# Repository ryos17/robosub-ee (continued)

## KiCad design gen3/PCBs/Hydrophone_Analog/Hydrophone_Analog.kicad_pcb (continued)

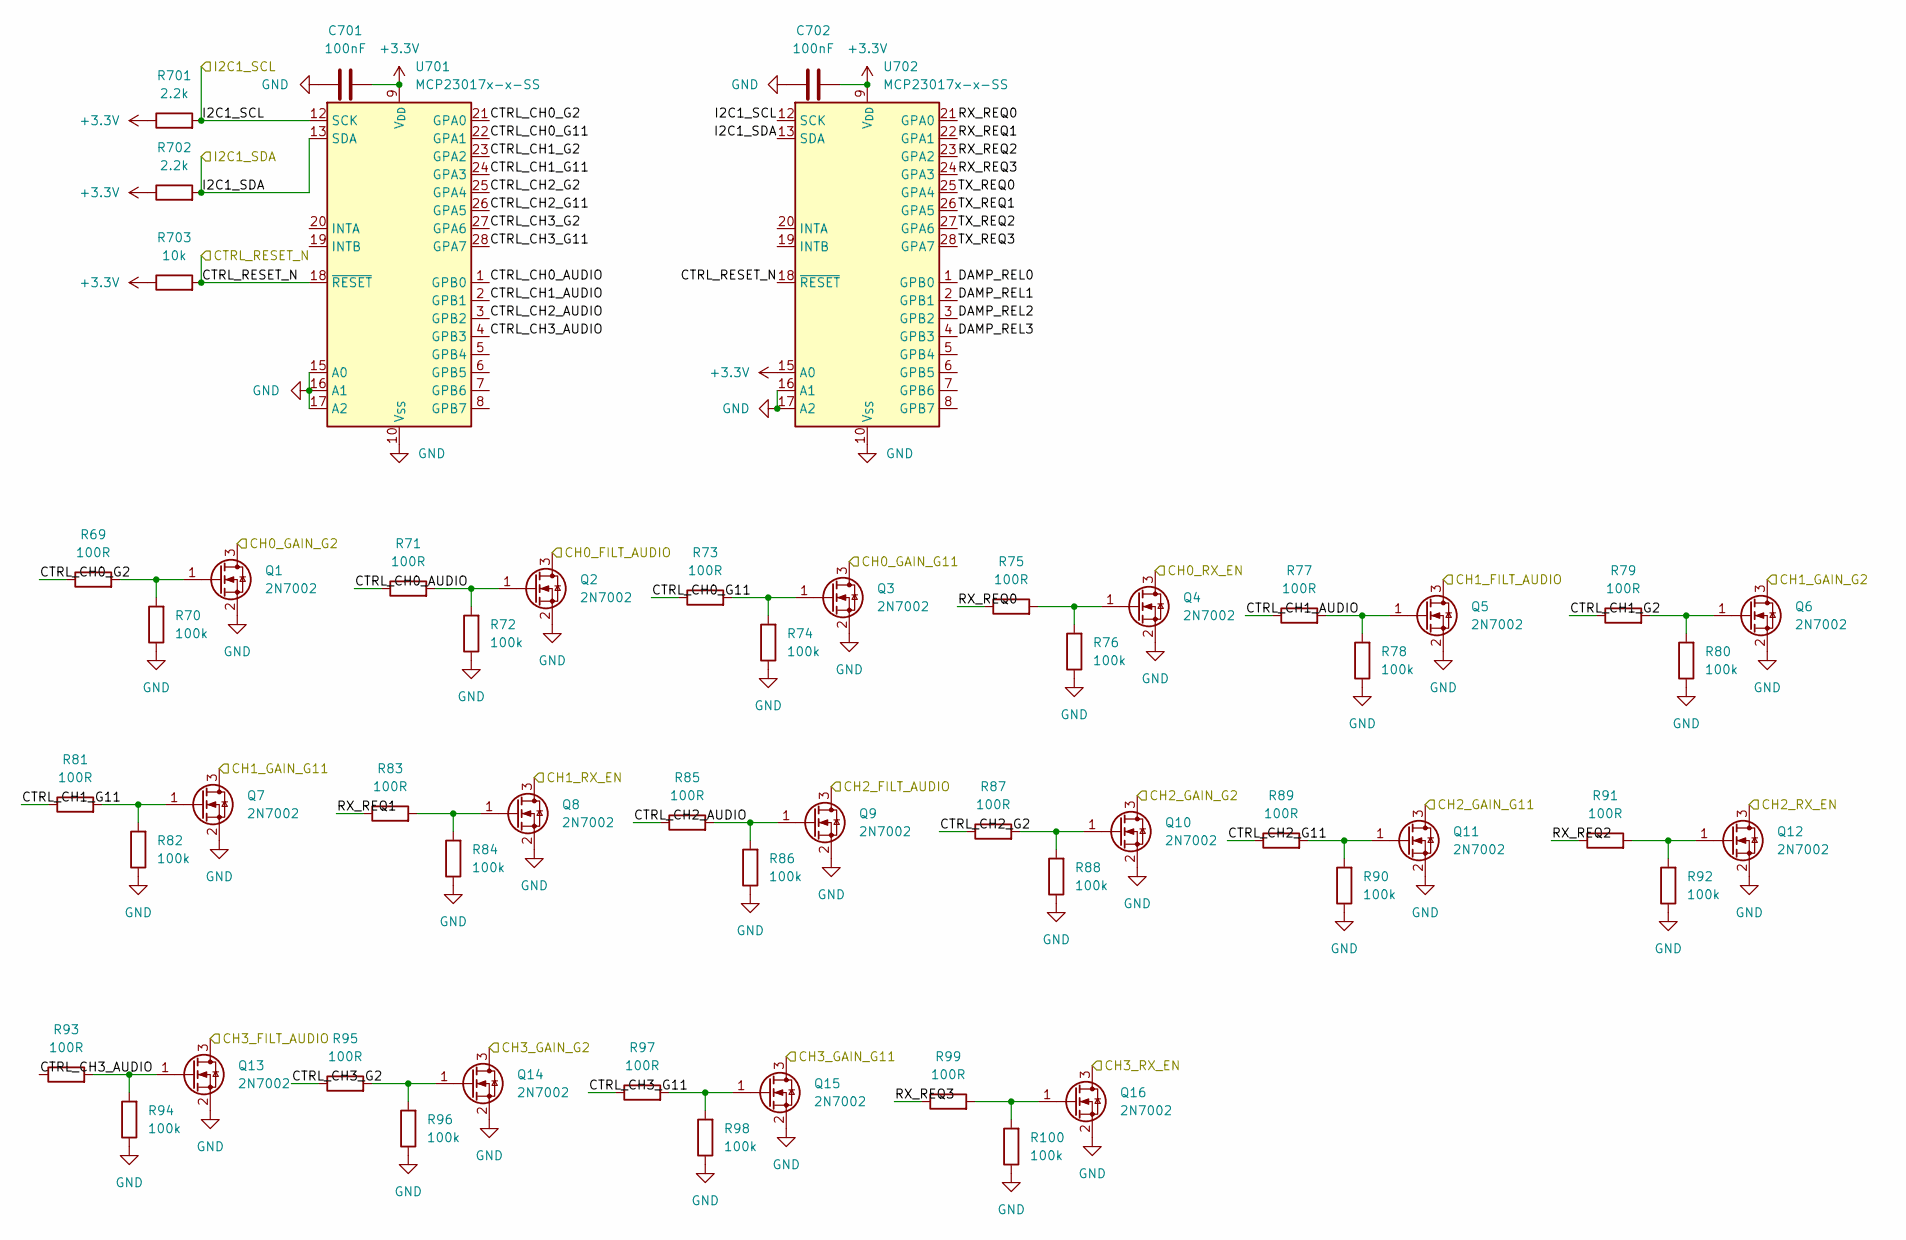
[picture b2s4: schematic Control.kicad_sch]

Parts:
C701, C702: 100nF; C_0805_2012Metric
Q1, Q2, Q3, Q4, Q5, Q6, Q7, Q8, Q9, Q10, Q11, Q12, Q13, Q14, Q15, Q16: 2N7002; SOT-23
R69, R71, R73, R75, R77, R79, R81, R83, R85, R87, R89, R91, R93, R95, R97, R99: 100R; R_0805_2012Metric
R70, R72, R74, R76, R78, R80, R82, R84, R86, R88, R90, R92, R94, R96, R98, R100: 100k; R_0805_2012Metric
R701, R702: 2.2k; R_0805_2012Metric
R703: 10k; R_0805_2012Metric
U701, U702: MCP23017x-x-SS; SSOP-28_5.3x10.2mm_P0.65mm

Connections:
+3.3V: C701.2, C702.2, R701.1, R702.1, R703.1, U701.9 (V_{DD}), U702.9 (V_{DD}), U702.15 (A0); also elsewhere on the board
/CH0_FILT_AUDIO: Q2.3 (D); also elsewhere on the board
/CH0_GAIN_G2: Q1.3 (D); also elsewhere on the board
/CH0_GAIN_G11: Q3.3 (D); also elsewhere on the board
/CH0_RX_EN: Q4.3 (D); also elsewhere on the board
/CH1_FILT_AUDIO: Q5.3 (D); also elsewhere on the board
/CH1_GAIN_G2: Q6.3 (D); also elsewhere on the board
/CH1_GAIN_G11: Q7.3 (D); also elsewhere on the board
/CH1_RX_EN: Q8.3 (D); also elsewhere on the board
/CH2_FILT_AUDIO: Q9.3 (D); also elsewhere on the board
/CH2_GAIN_G2: Q10.3 (D); also elsewhere on the board
/CH2_GAIN_G11: Q11.3 (D); also elsewhere on the board
/CH2_RX_EN: Q12.3 (D); also elsewhere on the board
/CH3_FILT_AUDIO: Q13.3 (D); also elsewhere on the board
/CH3_GAIN_G2: Q14.3 (D); also elsewhere on the board
/CH3_GAIN_G11: Q15.3 (D); also elsewhere on the board
/CH3_RX_EN: Q16.3 (D); also elsewhere on the board
/CTRL_RESET_N: R703.2, U701.18 (~RESET), U702.18 (~RESET); also elsewhere on the board
/Control/CTRL_CH0_AUDIO: R71.1, U701.1 (GPB0)
/Control/CTRL_CH0_G2: R69.1, U701.21 (GPA0)
/Control/CTRL_CH0_G11: R73.1, U701.22 (GPA1)
/Control/CTRL_CH1_AUDIO: R77.1, U701.2 (GPB1)
/Control/CTRL_CH1_G2: R79.1, U701.23 (GPA2)
/Control/CTRL_CH1_G11: R81.1, U701.24 (GPA3)
/Control/CTRL_CH2_AUDIO: R85.1, U701.3 (GPB2)
/Control/CTRL_CH2_G2: R87.1, U701.25 (GPA4)
/Control/CTRL_CH2_G11: R89.1, U701.26 (GPA5)
/Control/CTRL_CH3_AUDIO: R93.1, U701.4 (GPB3)
/Control/CTRL_CH3_G2: R95.1, U701.27 (GPA6)
/Control/CTRL_CH3_G11: R97.1, U701.28 (GPA7)
/Control/DAMP_REL0: U702.1 (GPB0)
/Control/DAMP_REL1: U702.2 (GPB1)
/Control/DAMP_REL2: U702.3 (GPB2)
/Control/DAMP_REL3: U702.4 (GPB3)
/Control/RX_REQ0: R75.1, U702.21 (GPA0)
/Control/RX_REQ1: R83.1, U702.22 (GPA1)
/Control/RX_REQ2: R91.1, U702.23 (GPA2)
/Control/RX_REQ3: R99.1, U702.24 (GPA3)
/Control/TX_REQ0: U702.25 (GPA4)
/Control/TX_REQ1: U702.26 (GPA5)
/Control/TX_REQ2: U702.27 (GPA6)
/Control/TX_REQ3: U702.28 (GPA7)
/I2C1_SCL: R701.2, U701.12 (SCK), U702.12 (SCK); also elsewhere on the board
/I2C1_SDA: R702.2, U701.13 (SDA), U702.13 (SDA); also elsewhere on the board
GND: C701.1, C702.1, Q1.2 (S), Q2.2 (S), Q3.2 (S), Q4.2 (S), Q5.2 (S), Q6.2 (S), Q7.2 (S), Q8.2 (S), Q9.2 (S), Q10.2 (S), Q11.2 (S), Q12.2 (S), Q13.2 (S), Q14.2 (S), Q15.2 (S), Q16.2 (S), R70.1, R72.1, R74.1, R76.1, R78.1, R80.1, R82.1, R84.1, R86.1, R88.1, R90.1, R92.1, R94.1, R96.1, R98.1, R100.1, U701.10 (V_{SS}), U701.15 (A0), U701.16 (A1), U701.17 (A2), U702.10 (V_{SS}), U702.16 (A1), U702.17 (A2); also elsewhere on the board
unnamed: Q1.1 (G), R69.2, R70.2
unnamed: Q2.1 (G), R71.2, R72.2
unnamed: Q3.1 (G), R73.2, R74.2
unnamed: Q4.1 (G), R75.2, R76.2
unnamed: Q5.1 (G), R77.2, R78.2
unnamed: Q6.1 (G), R79.2, R80.2
unnamed: Q7.1 (G), R81.2, R82.2
unnamed: Q8.1 (G), R83.2, R84.2
unnamed: Q9.1 (G), R85.2, R86.2
unnamed: Q10.1 (G), R87.2, R88.2
unnamed: Q11.1 (G), R89.2, R90.2
unnamed: Q12.1 (G), R91.2, R92.2
unnamed: Q13.1 (G), R93.2, R94.2
unnamed: Q14.1 (G), R95.2, R96.2
unnamed: Q15.1 (G), R97.2, R98.2
unnamed: Q16.1 (G), R99.2, R100.2

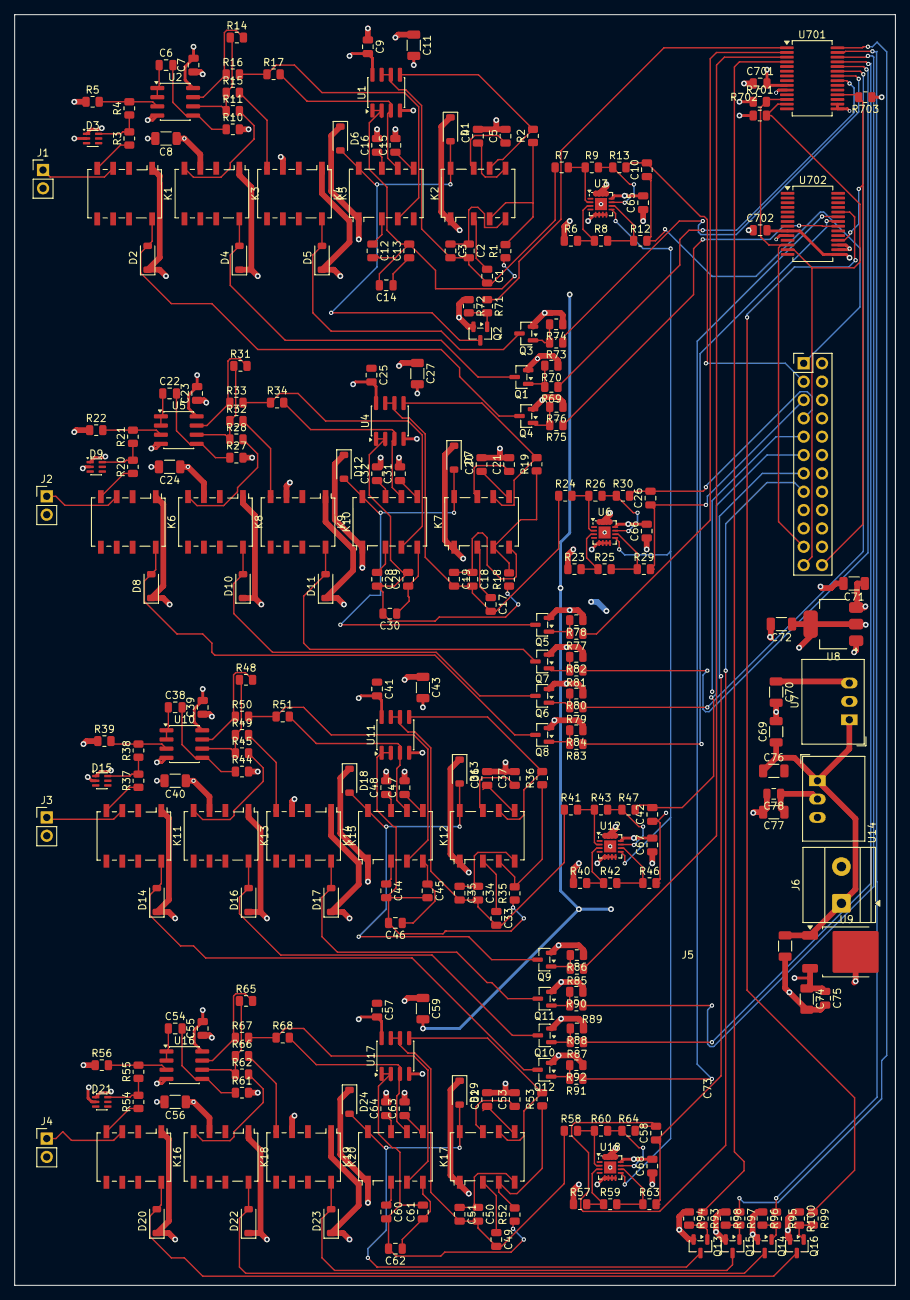
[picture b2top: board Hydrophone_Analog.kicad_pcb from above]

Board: 4 copper layers, 121.9 x 175.9 mm, 267 parts (0 on the bottom side), 178 nets.

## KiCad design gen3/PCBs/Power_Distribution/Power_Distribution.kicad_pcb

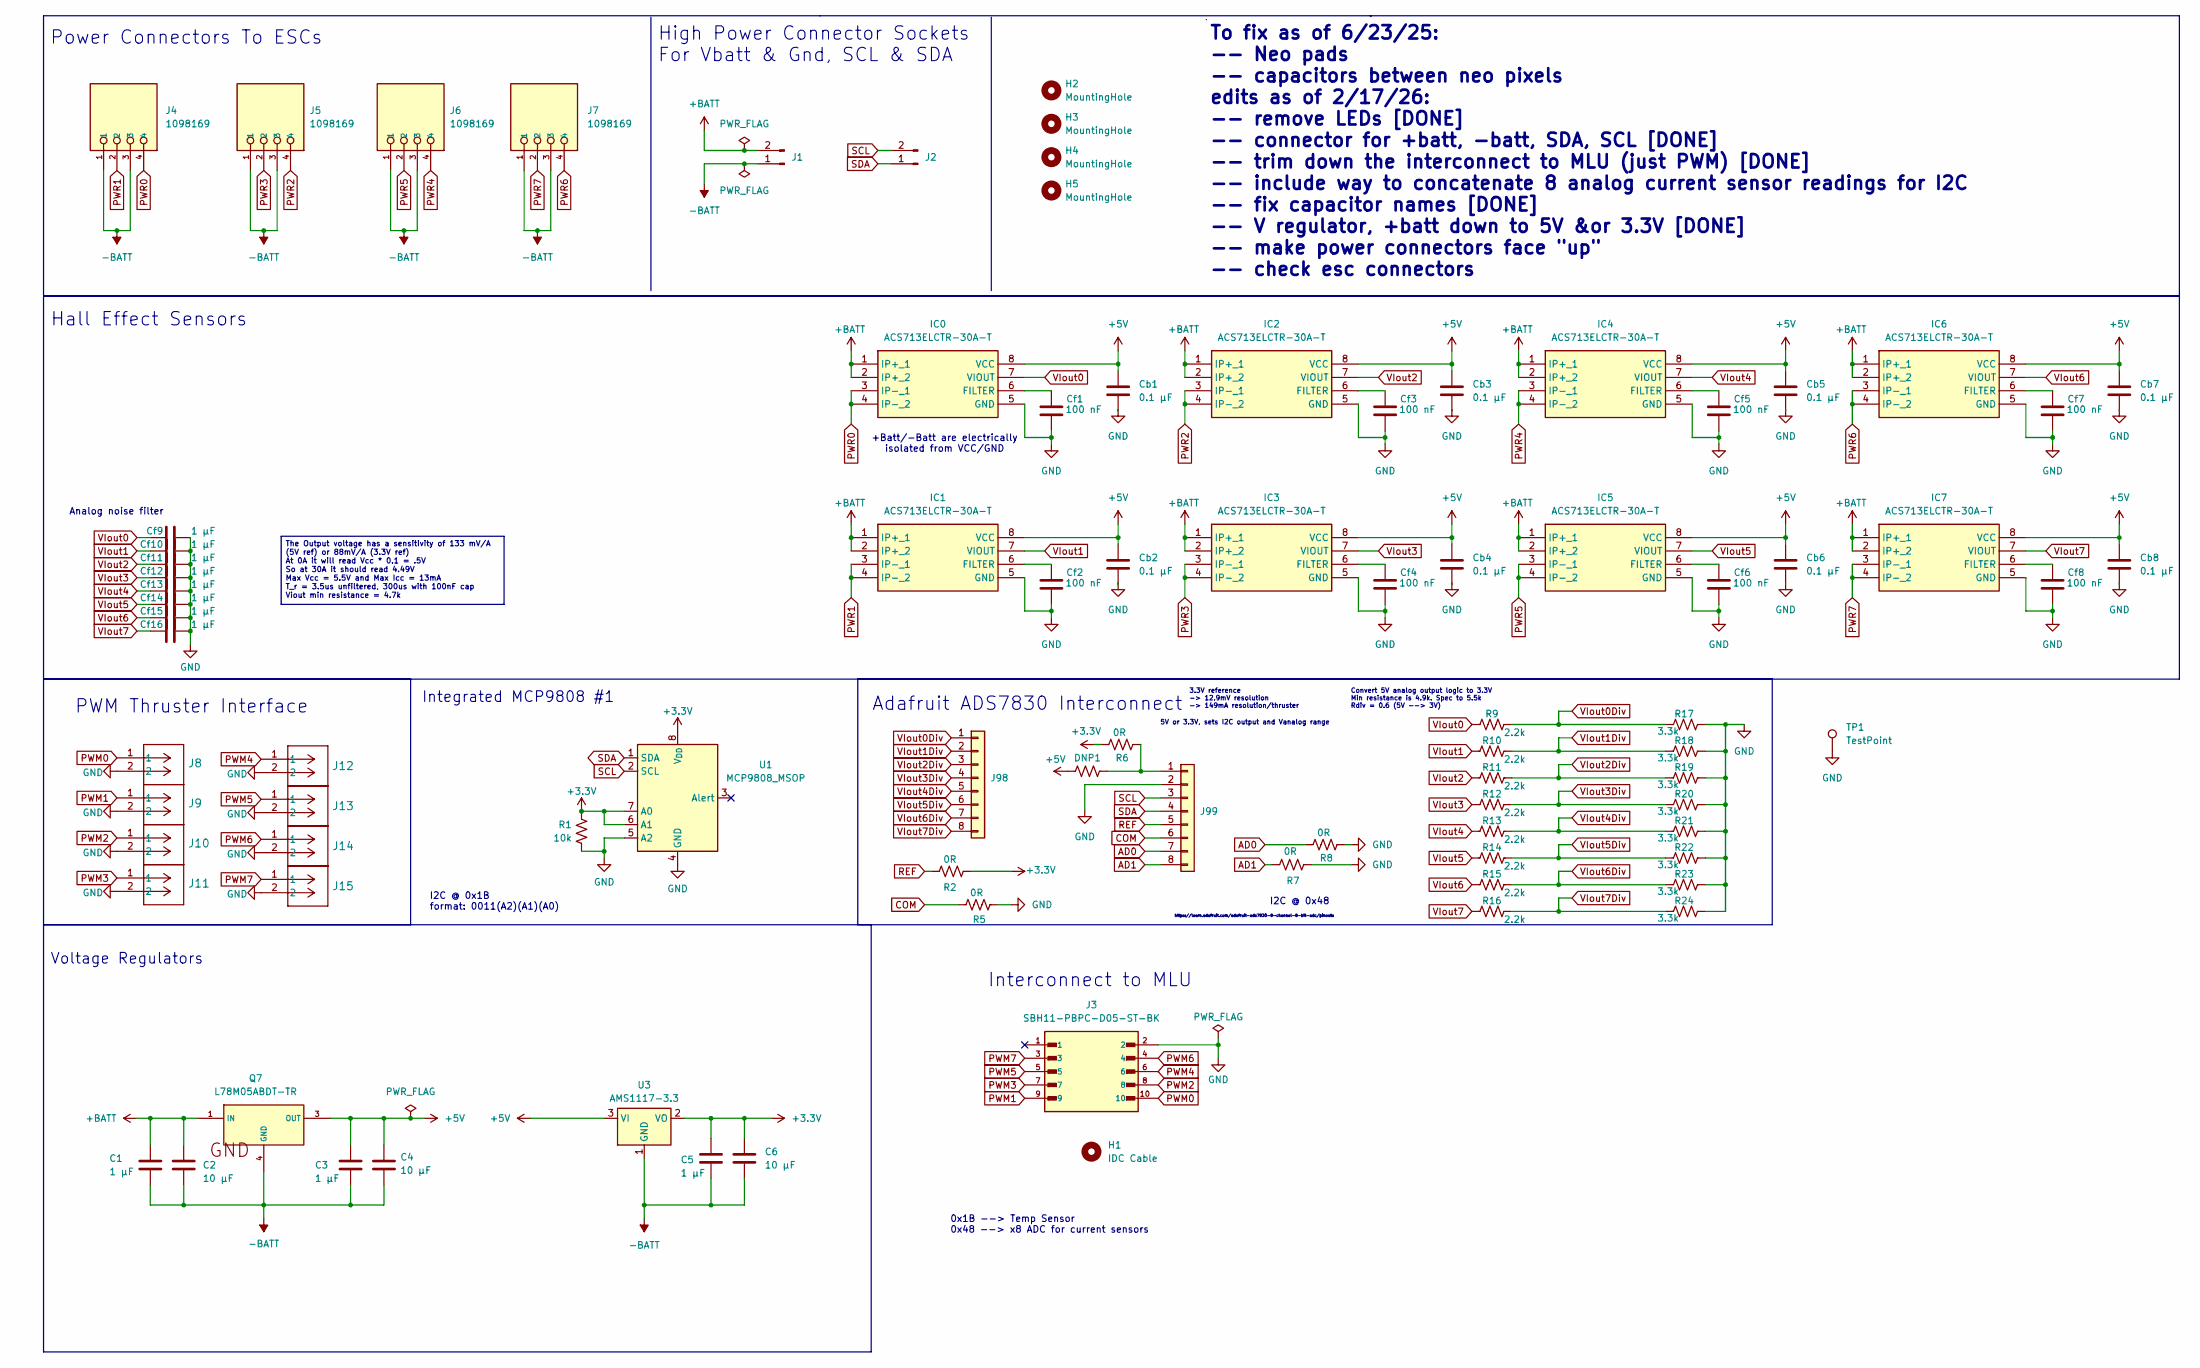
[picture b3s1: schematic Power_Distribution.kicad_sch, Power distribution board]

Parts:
C1, C3, C5: 1 µF; C_0805_2012Metric
C2, C4, C6: 10 µF; C_0805_2012Metric
Cb1, Cb2, Cb3, Cb4, Cb5, Cb6, Cb7, Cb8: 0.1 µF; C_0805_2012Metric_Pad1.18x1.45mm_HandSolder
Cf1, Cf2, Cf3, Cf4, Cf5, Cf6, Cf7, Cf8: 100 nF; C_0805_2012Metric_Pad1.18x1.45mm_HandSolder
Cf9, Cf10, Cf11, Cf12, Cf13, Cf14, Cf15, Cf16: 1 µF; C_0805_2012Metric_Pad1.18x1.45mm_HandSolder
DNP1: 0; R_0805_2012Metric
H1: IDC Cable
H2, H3, H4, H5: MountingHole; MountingHole_4.3mm_M4
IC0, IC1, IC2, IC3, IC4, IC5, IC6, IC7: ACS713ELCTR-30A-T; ACS711ELCTR25ABT; Manufacturer_Part_Number ACS713ELCTR-30A-T
J1: Conn_01x02_Pin; AMASS_XT60IPW-M_1x03_P7.20mm_Horizontal
J2: Conn_01x02_Pin; AMASS_XT30PW-F_1x02_P2.50mm_Horizontal
J3: SBH11-PBPC-D05-ST-BK; SULLINS_SBH11-PBPC-D05-ST-BK; PARTREV J
J4, J5, J6, J7: 1098169; PHOENIX_1098169
J8, J9, J10, J11, J12, J13, J14, J15: 430450212; Molex_Micro-Fit_3.0_43045-0212_2x01_P3.00mm_Vertical
J98, J99: Conn_01x08; PinHeader_1x08_P2.54mm_Vertical
Q7: L78M05ABDT-TR; TO-252-2_L6.5-W6.1-P4.58-LS10.0-TL; LCSC C58069
R1: 10k; R_0805_2012Metric_Pad1.20x1.40mm_HandSolder
R2, R5, R6, R7, R8: 0R; R_0805_2012Metric_Pad1.20x1.40mm_HandSolder
R9, R10, R11, R12, R13, R14, R15, R16: 2.2k; R_0805_2012Metric
R17, R18, R19, R20, R21, R22, R23, R24: 3.3k; R_0805_2012Metric
TP1: TestPoint; TestPoint_Keystone_5019_Miniature
U1: MCP9808_MSOP; MSOP-8_3x3mm_P0.65mm
U3: AMS1117-3.3; SOT-223-3_TabPin2

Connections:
+3.3V: C5.1, C6.1, R1.1, R2.2, R6.1, U1.6 (A1), U1.7 (A0), U1.8 (V_{DD}), U3.2 (VO)
+5V: C3.1, C4.1, Cb1.1, Cb2.1, Cb3.1, Cb4.1, Cb5.1, Cb6.1, Cb7.1, Cb8.1, DNP1.1, IC0.8 (VCC), IC1.8 (VCC), IC2.8 (VCC), IC3.8 (VCC), IC4.8 (VCC), IC5.8 (VCC), IC6.8 (VCC), IC7.8 (VCC), Q7.3 (OUT), U3.3 (VI)
+BATT: C1.1, C2.1, IC0.1 (IP+_1), IC0.2 (IP+_2), IC1.1 (IP+_1), IC1.2 (IP+_2), IC2.1 (IP+_1), IC2.2 (IP+_2), IC3.1 (IP+_1), IC3.2 (IP+_2), IC4.1 (IP+_1), IC4.2 (IP+_2), IC5.1 (IP+_1), IC5.2 (IP+_2), IC6.1 (IP+_1), IC6.2 (IP+_2), IC7.1 (IP+_1), IC7.2 (IP+_2), J1.2, Q7.1 (IN)
-BATT: C1.2, C2.2, C3.2, C4.2, C5.2, C6.2, J1.1, J4.1, J4.3, J5.1, J5.3, J6.1, J6.3, J7.1, J7.3, Q7.4 (GND), U3.1 (GND)
AD0: J99.7, R8.1
AD1: J99.8, R7.1
COM: J99.6, R5.1
GND: Cb1.2, Cb2.2, Cb3.2, Cb4.2, Cb5.2, Cb6.2, Cb7.2, Cb8.2, Cf1.2, Cf2.2, Cf3.2, Cf4.2, Cf5.2, Cf6.2, Cf7.2, Cf8.2, Cf9.2, Cf10.2, Cf11.2, Cf12.2, Cf13.2, Cf14.2, Cf15.2, Cf16.2, IC0.5 (GND), IC1.5 (GND), IC2.5 (GND), IC3.5 (GND), IC4.5 (GND), IC5.5 (GND), IC6.5 (GND), IC7.5 (GND), J3.2, J8.2, J9.2, J10.2, J11.2, J12.2, J13.2, J14.2, J15.2, J99.2, R1.2, R5.2, R7.2, R8.2, R17.2, R18.2, R19.2, R20.2, R21.2, R22.2, R23.2, R24.2, TP1.1, U1.4 (GND), U1.5 (A2)
unnamed: Cf1.1, IC0.6 (FILTER)
unnamed: Cf2.1, IC1.6 (FILTER)
unnamed: Cf3.1, IC2.6 (FILTER)
unnamed: Cf4.1, IC3.6 (FILTER)
unnamed: Cf5.1, IC4.6 (FILTER)
unnamed: Cf6.1, IC5.6 (FILTER)
unnamed: Cf7.1, IC6.6 (FILTER)
unnamed: Cf8.1, IC7.6 (FILTER)
unnamed: DNP1.2, J99.1, R6.2
PWM0: J3.10, J8.1
PWM1: J3.9, J9.1
PWM2: J3.8, J10.1
PWM3: J3.7, J11.1
PWM4: J3.6, J12.1
PWM5: J3.5, J13.1
PWM6: J3.4, J14.1
PWM7: J3.3, J15.1
PWR0: IC0.3 (IP-_1), IC0.4 (IP-_2), J4.4
PWR1: IC1.3 (IP-_1), IC1.4 (IP-_2), J4.2
PWR2: IC2.3 (IP-_1), IC2.4 (IP-_2), J5.4
PWR3: IC3.3 (IP-_1), IC3.4 (IP-_2), J5.2
PWR4: IC4.3 (IP-_1), IC4.4 (IP-_2), J6.4
PWR5: IC5.3 (IP-_1), IC5.4 (IP-_2), J6.2
PWR6: IC6.3 (IP-_1), IC6.4 (IP-_2), J7.4
PWR7: IC7.3 (IP-_1), IC7.4 (IP-_2), J7.2
REF: J99.5, R2.1
SCL: J2.2, J99.3, U1.2 (SCL)
SDA: J2.1, J99.4, U1.1 (SDA)
VIout0: Cf9.1, IC0.7 (VIOUT), R9.1
VIout0Div: J98.1, R9.2, R17.1
VIout1: Cf10.1, IC1.7 (VIOUT), R10.1
VIout1Div: J98.2, R10.2, R18.1
VIout2: Cf11.1, IC2.7 (VIOUT), R11.1
VIout2Div: J98.3, R11.2, R19.1
VIout3: Cf12.1, IC3.7 (VIOUT), R12.1
VIout3Div: J98.4, R12.2, R20.1
VIout4: Cf13.1, IC4.7 (VIOUT), R13.1
VIout4Div: J98.5, R13.2, R21.1
VIout5: Cf14.1, IC5.7 (VIOUT), R14.1
VIout5Div: J98.6, R14.2, R22.1
VIout6: Cf15.1, IC6.7 (VIOUT), R15.1
VIout6Div: J98.7, R15.2, R23.1
VIout7: Cf16.1, IC7.7 (VIOUT), R16.1
VIout7Div: J98.8, R16.2, R24.1

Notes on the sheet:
Interconnect to MLU
Convert 5V analog output logic to 3.3V Min resistance is 4.9k. Spec to 5.5k Rdiv = 0.6 (5V --> 3V)
Analog noise filter
+Batt/-Batt are electrically isolated from VCC/GND
https://learn.adafruit.com/adafruit-ads7830-8-channel-8-bit-adc/pinouts
To fix as of 6/23/25: -- Neo pads -- capacitors between neo pixels edits as of 2/17/26: -- remove LEDs [DONE] -- connector for +batt, -batt, SDA, SCL [DONE] -- trim down the interconnect to MLU (just PWM) [DONE] -- include way to concatenate 8 analog current sensor readings for I2C -- fix capacitor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
I2C @ 0x48
Adafruit ADS7830 Interconnect
5V or 3.3V, sets I2C output and Vanalog range
0x1B --> Temp Sensor 0x48 --> x8 ADC for current sensors
High Power Connector Sockets For Vbatt & Gnd, SCL & SDA
Voltage Regulators
Integrated MCP9808 #1
Power Connectors To ESCs
3.3V reference -> 12.9mV resolution -> 149mA resolution/thruster
PWM Thruster Interface
I2C @ 0x1B format: 0011(A2)(A1)(A0)
Hall Effect Sensors
The Output voltage has a sensitivity of 133 mV/A (5V ref) or 88mV/A (3.3V ref) At 0A it will read Vcc * 0.1 = .5V So at 30A it should read 4.49V Max Vcc = 5.5V and Max Icc = 13mA T_r = 3.5us unfiltered, 300us with 100nF cap Viout min resistance = 4.7k

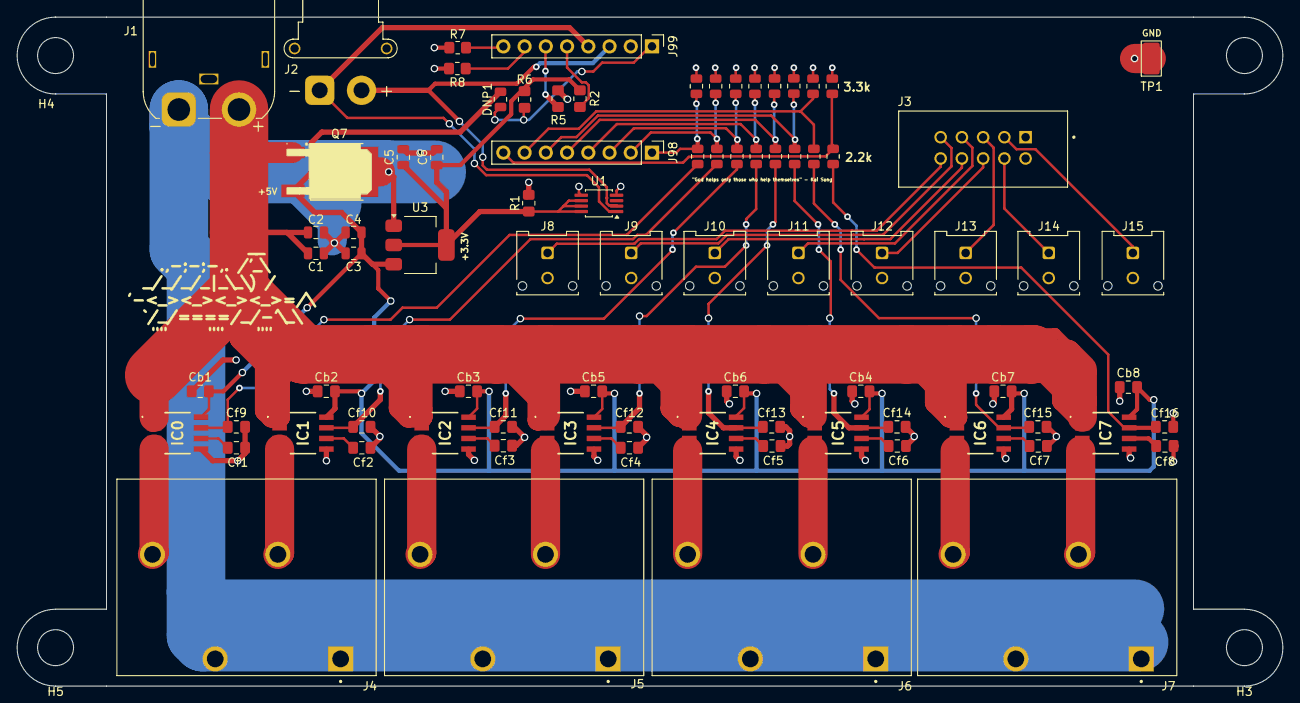
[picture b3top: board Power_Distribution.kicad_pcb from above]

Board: 2 copper layers, 151.4 x 80.0 mm, 86 parts (0 on the bottom side), 52 nets.

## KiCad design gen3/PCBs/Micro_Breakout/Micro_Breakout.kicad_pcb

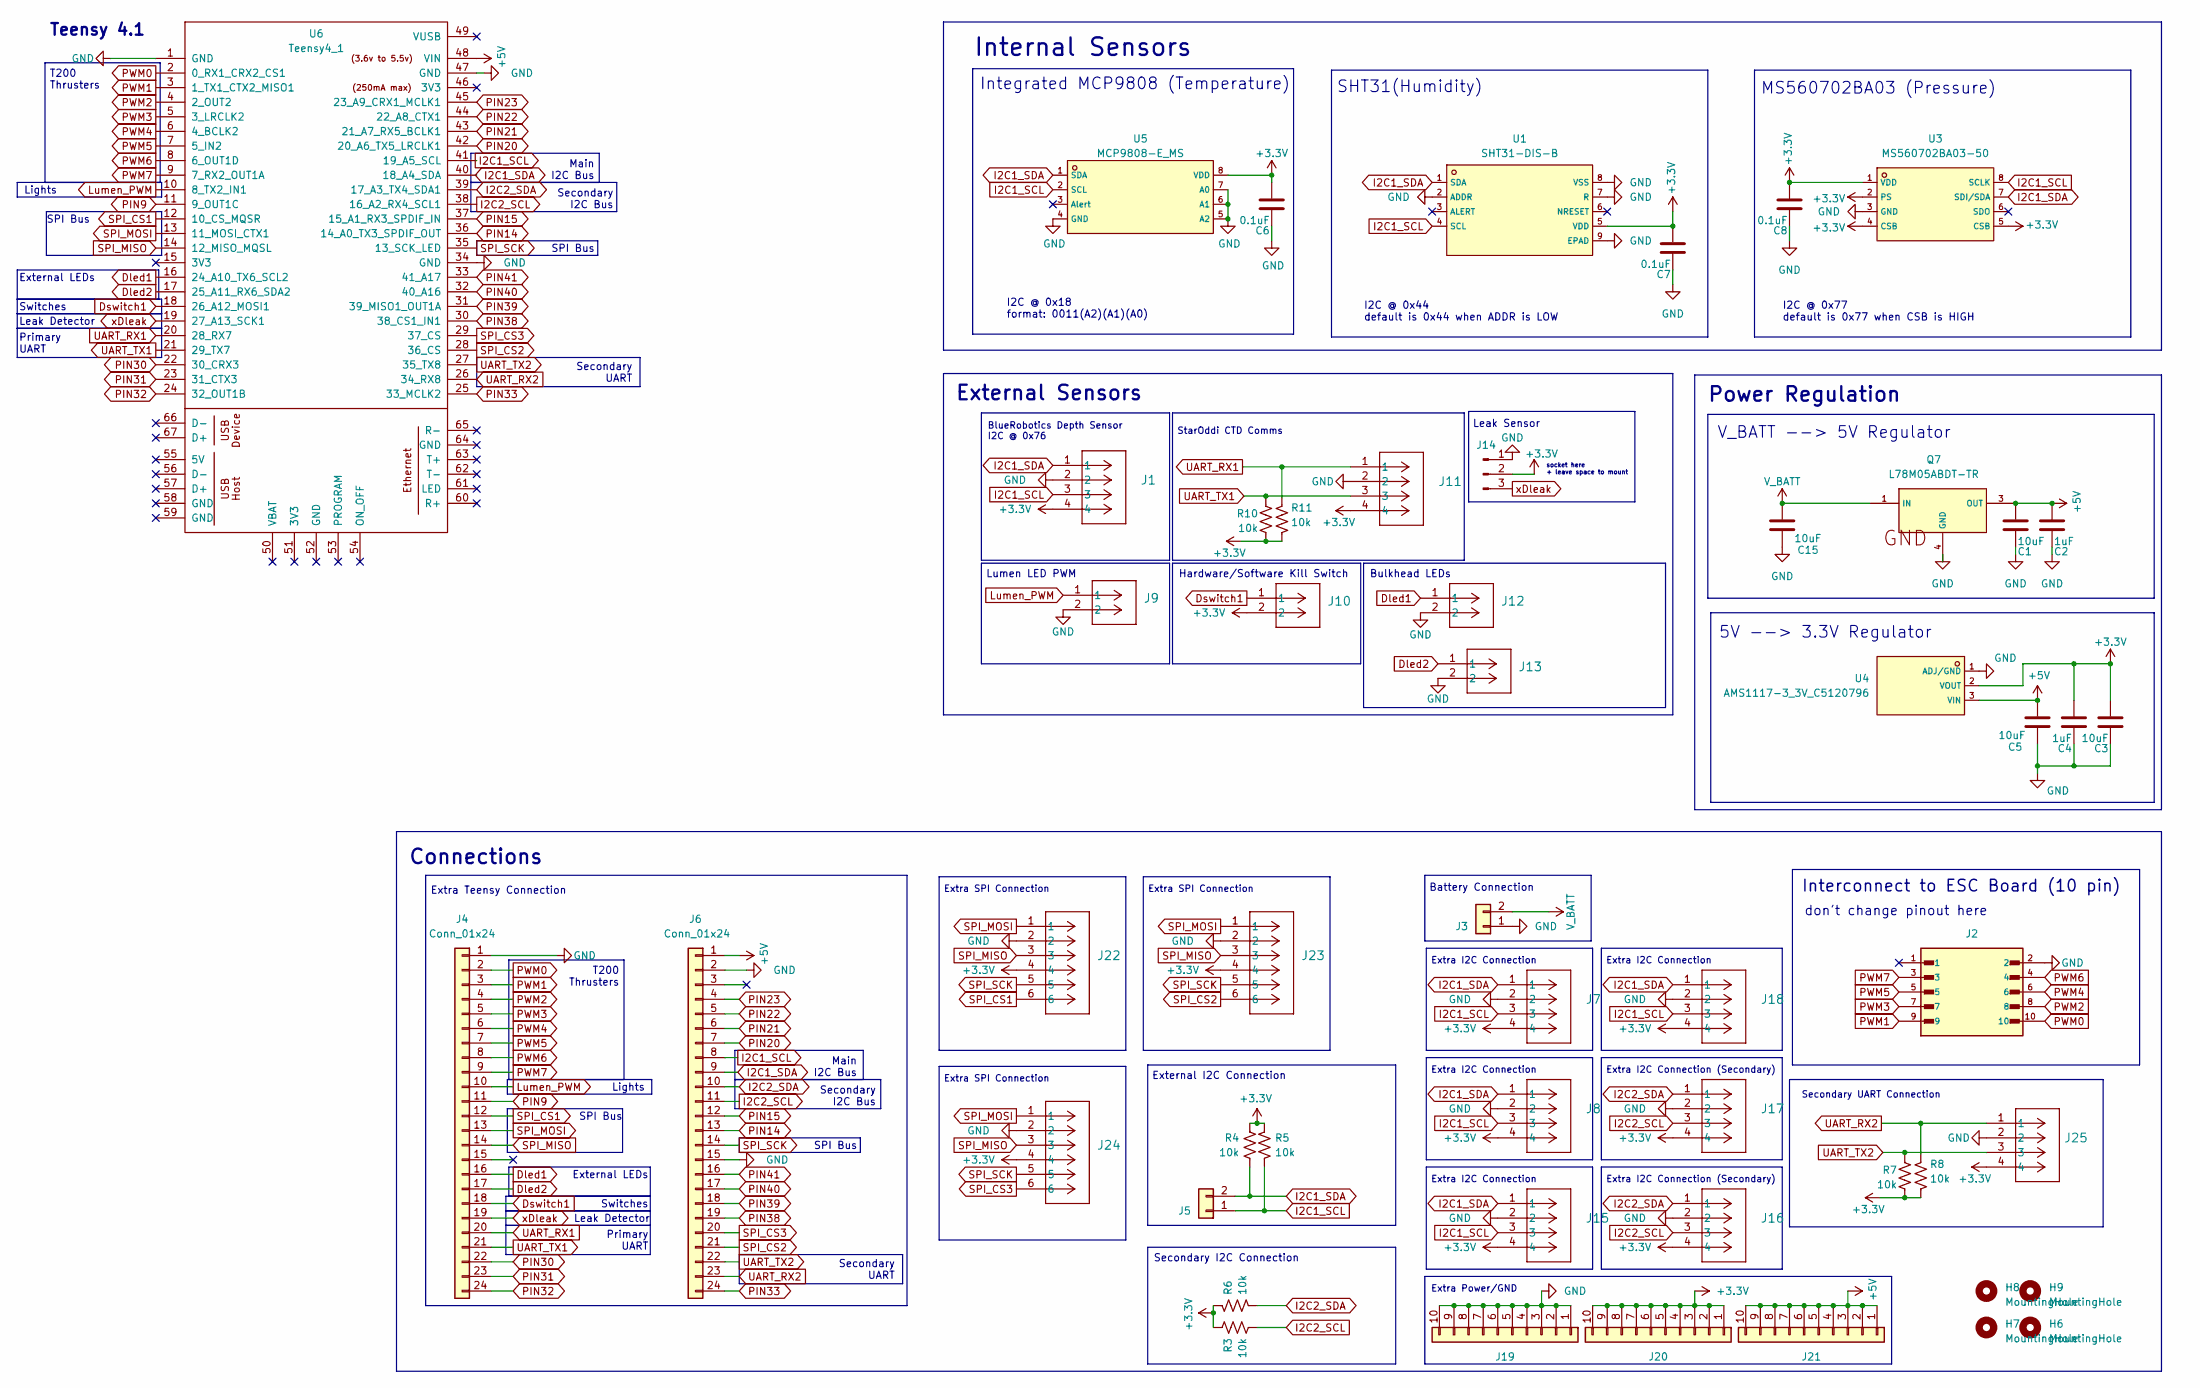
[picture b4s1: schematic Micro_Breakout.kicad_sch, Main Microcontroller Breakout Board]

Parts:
C1, C3, C5, C15: 10uF; C_0805_2012Metric_Pad1.18x1.45mm_HandSolder
C2, C4: 1uF; C_0805_2012Metric_Pad1.18x1.45mm_HandSolder
C6, C7, C8: 0.1uF; C_0805_2012Metric_Pad1.18x1.45mm_HandSolder
H6, H7, H8, H9: MountingHole; MountingHole_4.3mm_M4
J1: BlueRobotics Depth Sensor; 430450412
J2: Interconnect; SBH11-PBPC-D05-ST-BK; PARTREV J
J3: External Battery; AMASS_XT60PW-F_1x02_P7.20mm_Horizontal
J4, J6: Conn_01x24; PinHeader_1x24_P2.54mm_Vertical
J5: External I2C; AMASS_XT30PW-F_1x02_P2.50mm_Horizontal
J7: Extra I2C #1; 430450412
J8: Extra I2C #2; 430450412
J9: Lumen PWM; 430450212
J10: Kill Switch; 430450212
J11: StarOddi CTD Comms; 430450412
J12: LED1; 430450212
J13: LED2; 430450212
J14: Leak Sensor; PinHeader_1x03_P2.54mm_Vertical
J15: Extra I2C #3; 430450412
J16: Extra I2C #6; 430450412
J17: Extra I2C #5; 430450412
J18: Extra I2C #4; 430450412
J19: GND Line; PinHeader_1x10_P2.54mm_Vertical
J20: 3.3V Line; PinHeader_1x10_P2.54mm_Vertical
J21: 5V Line; PinHeader_1x10_P2.54mm_Vertical
J22: Extra SPI #1; 430450612
J23: Extra SPI #2; 430450612
J24: Extra SPI #3; 430450612
J25: Secondary UART; 430450412
Q7: L78M05ABDT-TR; LCSC C58069
R3, R4, R5, R6, R7, R8, R10, R11: 10k; R_0805_2012Metric_Pad1.20x1.40mm_HandSolder
U1: SHT31-DIS-B; LCSC C80862
U3: MS560702BA03-50; LCSC C97627
U4: AMS1117-3_3V_C5120796; LCSC C5120796
U5: MCP9808-E_MS; LCSC C94847
U6: Teensy4_1

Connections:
+3.3V: C3.1, C4.1, C6.1, C7.1, C8.1, J1.4, J7.4, J8.4, J10.2, J11.4, J14.2, J15.4, J16.4, J17.4, J18.4, J20.1, J20.2, J20.3, J20.4, J20.5, J20.6, J20.7, J20.8, J20.9, J20.10, J22.4, J23.4, J24.4, J25.4, R3.1, R4.1, R5.1, R6.1, R7.2, R8.2, R10.2, R11.2, U1.5 (VDD), U3.1 (VDD), U3.2 (PS), U3.4 (CSB), U3.5 (CSB), U4.2 (VOUT), U5.8 (VDD)
+5V: C1.1, C2.1, C5.1, J6.1, J21.1, J21.2, J21.3, J21.4, J21.5, J21.6, J21.7, J21.8, J21.9, J21.10, Q7.3 (OUT), U4.3 (VIN), U6.48 (VIN)
Dled1: J4.16, J12.1, U6.16 (24_A10_TX6_SCL2)
Dled2: J4.17, J13.1, U6.17 (25_A11_RX6_SDA2)
Dswitch1: J4.18, J10.1, U6.18 (26_A12_MOSI1)
GND: C1.2, C2.2, C3.2, C4.2, C5.2, C6.2, C7.2, C8.2, C15.2, J1.2, J2.2, J3.1, J4.1, J6.2, J6.15, J7.2, J8.2, J9.2, J11.2, J12.2, J13.2, J14.1, J15.2, J16.2, J17.2, J18.2, J19.1, J19.2, J19.3, J19.4, J19.5, J19.6, J19.7, J19.8, J19.9, J19.10, J22.2, J23.2, J24.2, J25.2, Q7.4 (GND), U1.2 (ADDR), U1.7 (R), U1.8 (VSS), U1.9 (EPAD), U3.3 (GND), U4.1 (ADJ/GND), U5.4 (GND), U5.5 (A2), U5.6 (A1), U5.7 (A0), U6.1 (GND), U6.34 (GND), U6.47 (GND)
I2C1_SCL: J1.3, J5.1, J6.8, J7.3, J8.3, J15.3, J18.3, R5.2, U1.4 (SCL), U3.8 (SCLK), U5.2 (SCL), U6.41 (19_A5_SCL)
I2C1_SDA: J1.1, J5.2, J6.9, J7.1, J8.1, J15.1, J18.1, R4.2, U1.1 (SDA), U3.7 (SDI/SDA), U5.1 (SDA), U6.40 (18_A4_SDA)
I2C2_SCL: J6.11, J16.3, J17.3, R3.2, U6.38 (16_A2_RX4_SCL1)
I2C2_SDA: J6.10, J16.1, J17.1, R6.2, U6.39 (17_A3_TX4_SDA1)
Lumen_PWM: J4.10, J9.1, U6.10 (8_TX2_IN1)
PIN9: J4.11, U6.11 (9_OUT1C)
PIN14: J6.13, U6.36 (14_A0_TX3_SPDIF_OUT)
PIN15: J6.12, U6.37 (15_A1_RX3_SPDIF_IN)
PIN20: J6.7, U6.42 (20_A6_TX5_LRCLK1)
PIN21: J6.6, U6.43 (21_A7_RX5_BCLK1)
PIN22: J6.5, U6.44 (22_A8_CTX1)
PIN23: J6.4, U6.45 (23_A9_CRX1_MCLK1)
PIN30: J4.22, U6.22 (30_CRX3)
PIN31: J4.23, U6.23 (31_CTX3)
PIN32: J4.24, U6.24 (32_OUT1B)
PIN33: J6.24, U6.25 (33_MCLK2)
PIN38: J6.19, U6.30 (38_CS1_IN1)
PIN39: J6.18, U6.31 (39_MISO1_OUT1A)
PIN40: J6.17, U6.32 (40_A16)
PIN41: J6.16, U6.33 (41_A17)
PWM0: J2.10, J4.2, U6.2 (0_RX1_CRX2_CS1)
PWM1: J2.9, J4.3, U6.3 (1_TX1_CTX2_MISO1)
PWM2: J2.8, J4.4, U6.4 (2_OUT2)
PWM3: J2.7, J4.5, U6.5 (3_LRCLK2)
PWM4: J2.6, J4.6, U6.6 (4_BCLK2)
PWM5: J2.5, J4.7, U6.7 (5_IN2)
PWM6: J2.4, J4.8, U6.8 (6_OUT1D)
PWM7: J2.3, J4.9, U6.9 (7_RX2_OUT1A)
SPI_CS1: J4.12, J22.6, U6.12 (10_CS_MQSR)
SPI_CS2: J6.21, J23.6, U6.28 (36_CS)
SPI_CS3: J6.20, J24.6, U6.29 (37_CS)
SPI_MISO: J4.14, J22.3, J23.3, J24.3, U6.14 (12_MISO_MQSL)
SPI_MOSI: J4.13, J22.1, J23.1, J24.1, U6.13 (11_MOSI_CTX1)
SPI_SCK: J6.14, J22.5, J23.5, J24.5, U6.35 (13_SCK_LED)
UART_RX1: J4.20, J11.1, R11.1, U6.20 (28_RX7)
UART_RX2: J6.23, J25.1, R8.1, U6.26 (34_RX8)
UART_TX1: J4.21, J11.3, R10.1, U6.21 (29_TX7)
UART_TX2: J6.22, J25.3, R7.1, U6.27 (35_TX8)
V_BATT: C15.1, J3.2, Q7.1 (IN)
xDleak: J4.19, J14.3, U6.19 (27_A13_SCK1)

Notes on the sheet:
Secondary I2C Bus
Hardware/Software Kill Switch
don't change pinout here
Primary UART
External I2C Connection
Power Regulation
Extra SPI Connection
Extra I2C Connection
I2C @ 0x44 default is 0x44 when ADDR is LOW
I2C @ 0x77 default is 0x77 when CSB is HIGH
Switches
Battery Connection
Lumen LED PWM
StarOddi CTD Comms
T200 Thrusters
SHT31(Humidity)
Extra I2C Connection (Secondary)
External LEDs
5V --> 3.3V Regulator
Leak Detector
Secondary UART
Internal Sensors
BlueRobotics Depth Sensor I2C @ 0x76
Bulkhead LEDs
Lights
Main I2C Bus
I2C @ 0x18 format: 0011(A2)(A1)(A0)
socket here + leave space to mount
Interconnect to ESC Board (10 pin)
Secondary I2C Connection
Extra Power/GND
Connections
Teensy 4.1
Leak Sensor
SPI Bus
Secondary UART Connection
External Sensors
Extra Teensy Connection
MS560702BA03 (Pressure)
V_BATT --> 5V Regulator

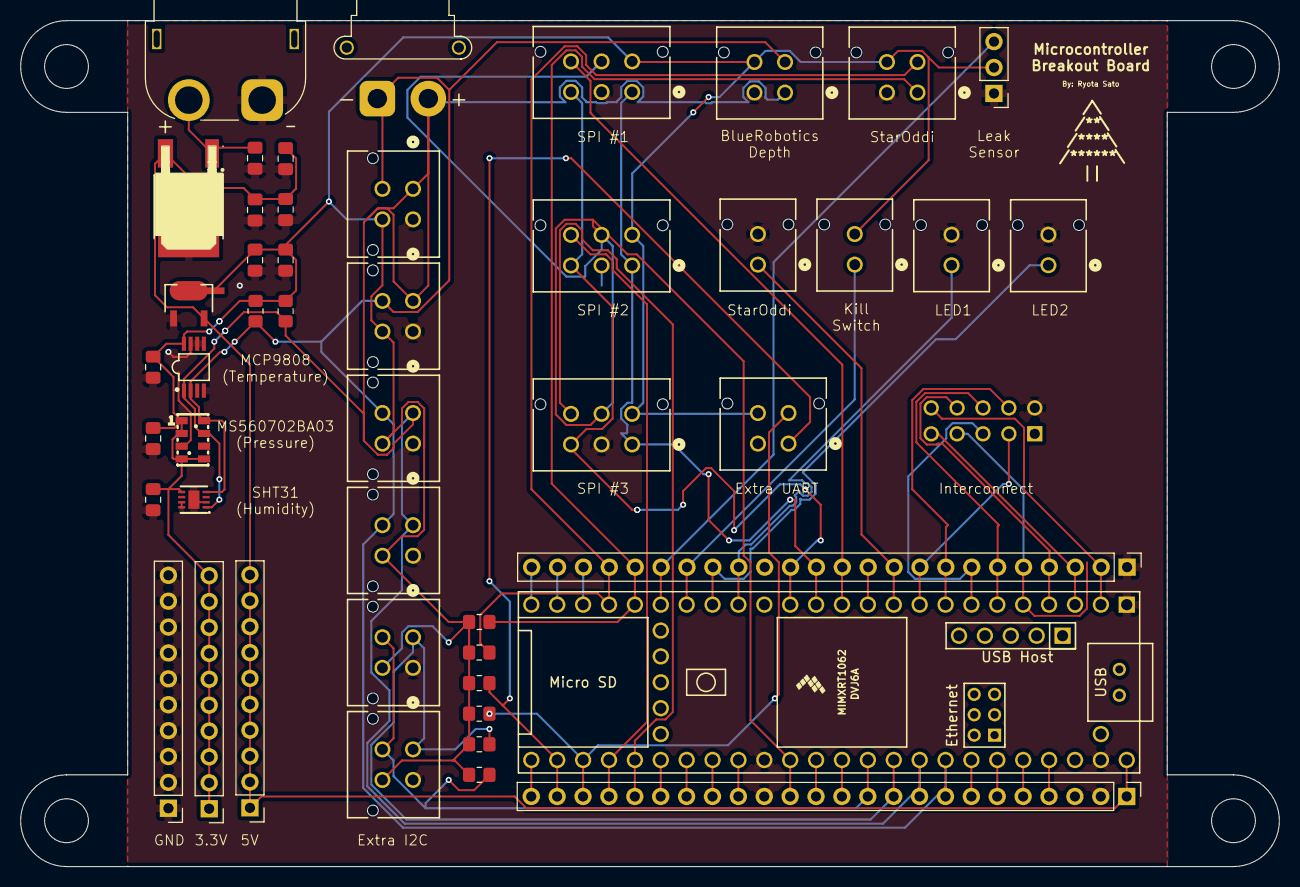
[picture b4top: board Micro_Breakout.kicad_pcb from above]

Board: 2 copper layers, 123.5 x 83.0 mm, 52 parts (1 on the bottom side), 46 nets.
